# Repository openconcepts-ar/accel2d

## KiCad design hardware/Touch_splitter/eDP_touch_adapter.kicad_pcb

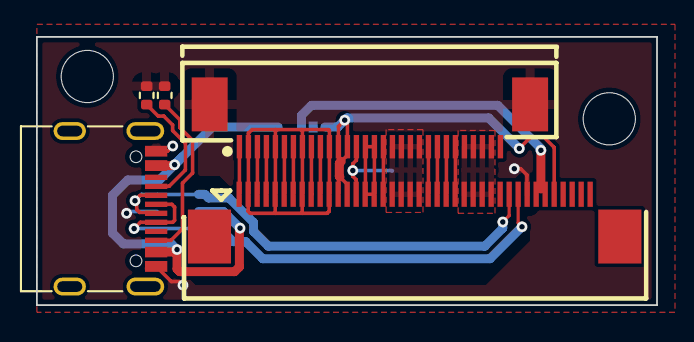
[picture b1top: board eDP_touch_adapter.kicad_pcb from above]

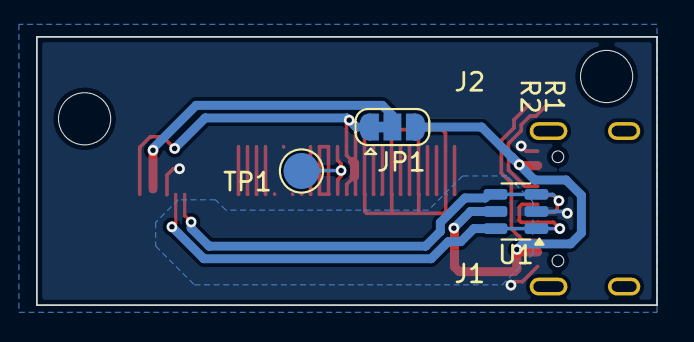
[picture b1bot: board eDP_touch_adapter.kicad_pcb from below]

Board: 2 copper layers, 34.4 x 14.9 mm, 10 parts (3 on the bottom side), 22 nets.

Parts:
H1, H2: MountingHole; MountingHole_2.2mm_M2_ISO7380
J1: Conn_01x40; FPC-SMD_40P-P0.50_L4.4-W25.6
J2: Conn_01x30; FPC-SMD_30P-P0.50_L4.4-W20.6
JP1: SolderJumper_3_Bridged12; SolderJumper-3_P1.3mm_Bridged12_RoundedPad1.0x1.5mm
R1, R2: 5.1k; R_0402_1005Metric
TP1: TestPoint_Small; TestPoint_Pad_D2.0mm
U1: USBLC6-2SC6; SOT-23-6
USB1: USB_C_Receptacle_USB2.0; USB_C_Receptacle_G-Switch_GT-USB-7010ASV

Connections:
+3V3: J1.12, J1.13, J1.36, J2.12, J2.13, JP1.1 (A)
+5V: JP1.3 (B), U1.5 (VBUS), USB1.A4 (VBUS), USB1.A9 (VBUS), USB1.B4 (VBUS), USB1.B9 (VBUS)
/AUX_N: J1.10, J2.10
/AUX_P: J1.9, J2.9
/BL_EN: J1.22, J2.22
/BL_GND: J1.18, J1.19, J1.20, J1.21, J2.18, J2.19, J2.20, J2.21
/BL_PWM: J1.23, J2.23
/BL_PWR: J1.26, J1.27, J1.28, J1.29, J2.26, J2.27, J2.28, J2.29
/EDP0_N: J1.6, J2.6
/EDP1_N: J1.3, J2.3
/EDP1_P: J1.4, J2.4
/EDPO_P: J1.7, J2.7
/HGND: J1.2, J1.5, J1.8, J1.11, J2.2, J2.5, J2.8, J2.11
/HPD: J1.17, J2.17
/LCD_GND: J1.15, J1.16, J2.15, J2.16
/TEST: J1.14, J2.14, TP1.1
/VTSP: J1.34, J1.35, JP1.2 (C)
GND: J1.33, J2.MP (MountPin), R1.2, R2.2, U1.2 (GND), USB1.A1 (GND), USB1.A12 (GND), USB1.B1 (GND), USB1.B12 (GND)
unnamed: R1.1, USB1.A5 (CC1)
unnamed: R2.1, USB1.B5 (CC2)
TP_D+: J1.32, U1.1 (I/O1), U1.6 (I/O1), USB1.A6 (D+), USB1.B6 (D+)
TP_D-: J1.31, U1.3 (I/O2), U1.4 (I/O2), USB1.A7 (D-), USB1.B7 (D-)

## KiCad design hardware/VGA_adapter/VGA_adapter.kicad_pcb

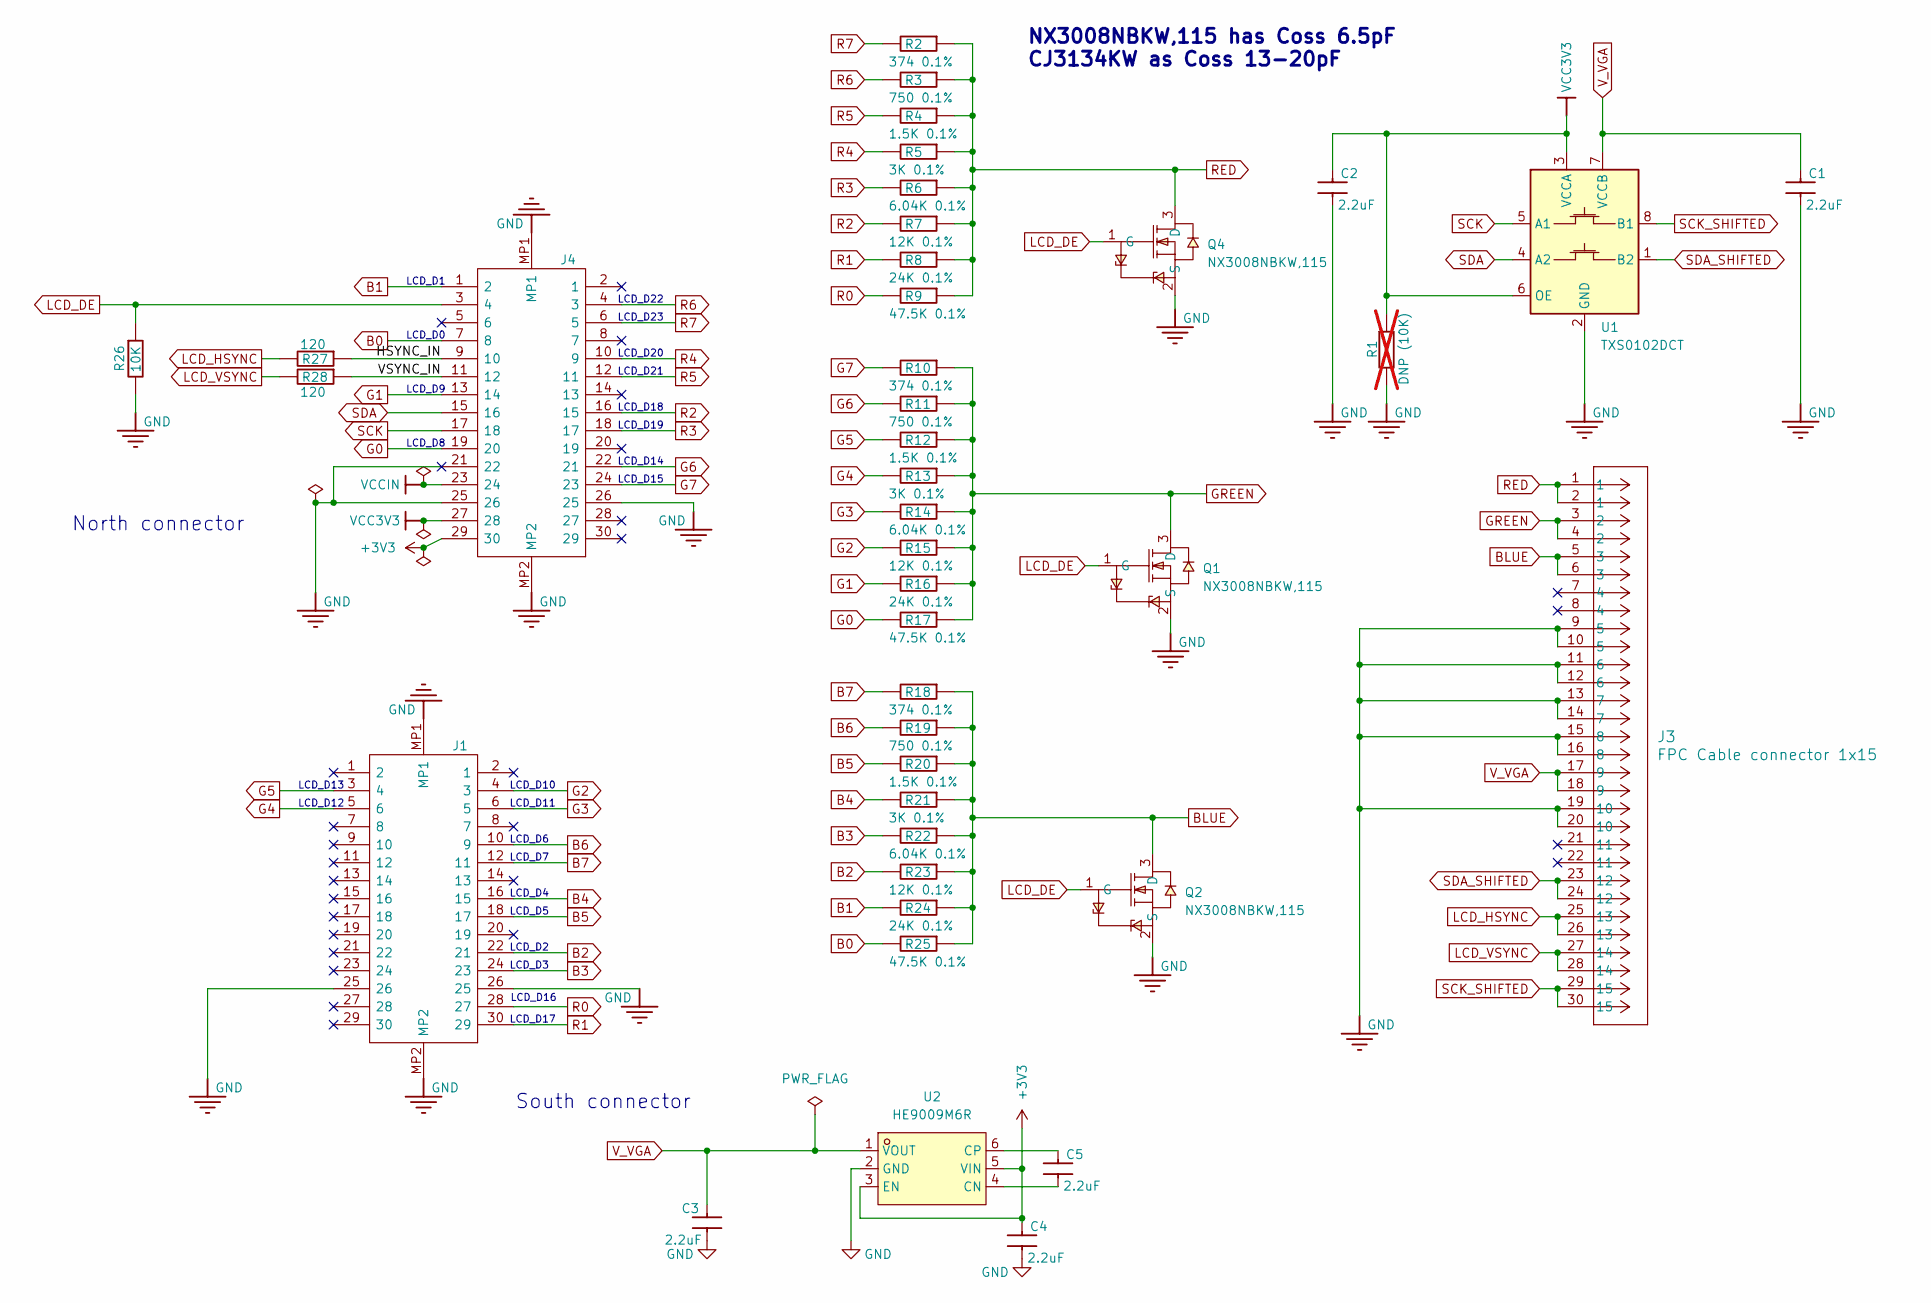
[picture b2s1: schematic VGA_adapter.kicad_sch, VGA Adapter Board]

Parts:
C1, C2, C3, C4, C5: 2.2uF; C_0402_1005Metric; LCSC Part Number C170151
J1, J4: DF12NB(3.0)-30DS-0.5V(51); CONN-SMD_30P-P0.50_HRS_DF12NB-3.0-30DP-0.5V; Manufacturer_Part_Number DF12NB(3.0)-30DP-0.5V(51); LCSC Part Number C2904115
J3: FPC Cable connector 1x15; TE Connectivity 1-1734248-5_ultralibrarian; LCSC Part Number C2922285
Q1, Q2, Q4: NX3008NBKW,115; SOT-323-3_L2.0-W1.3-P1.30-LS2.1-BR; MPN NX3008NBKW,115
R1: DNP (10K); R_0402_1005Metric; LCSC Part Number C25531; not fitted
R2, R10, R18: 374 0.1%; R_0402_1005Metric; LCSC Part Number C2681606
R3, R11, R19: 750 0.1%; R_0402_1005Metric; LCSC Part Number C852911
R4, R12, R20: 1.5K 0.1%; R_0402_1005Metric; LCSC Part Number C317917
R5, R13, R21: 3K 0.1%; R_0402_1005Metric; LCSC Part Number C281777
R6, R14, R22: 6.04K 0.1%; R_0402_1005Metric; LCSC Part Number C851092
R7, R15, R23: 12K 0.1%; R_0402_1005Metric; LCSC Part Number C319888
R8, R16, R24: 24K 0.1%; R_0402_1005Metric; LCSC Part Number C852665
R9, R17, R25: 47.5K 0.1%; R_0402_1005Metric; LCSC Part Number C2686413
R26: 10K; R_0402_1005Metric; LCSC Part Number C25531
R27, R28: 120; R_0402_1005Metric; LCSC Part Number C114758
U1: TXS0102DCT; SSOP-8_2.95x2.8mm_P0.65mm
U2: HE9009M6R; SOT-23-6; MPN HE9009M6R

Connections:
+3V3: C4.1, J4.29 (30), U2.3 (EN), U2.5 (VIN)
/HSYNC_IN: J4.9 (10), R27.1
/VSYNC_IN: J4.11 (12), R28.1
B0: J4.7 (8), R25.2
B1: J4.1 (2), R24.2
B2: J1.22 (21), R23.2
B3: J1.24 (23), R22.2
B4: J1.16 (15), R21.2
B5: J1.18 (17), R20.2
B6: J1.10 (9), R19.2
B7: J1.12 (11), R18.2
BLUE: J3.5 (3), J3.6 (3), Q2.3 (D), R18.1, R19.1, R20.1, R21.1, R22.1, R23.1, R24.1, R25.1
G0: J4.19 (20), R17.2
G1: J4.13 (14), R16.2
G2: J1.4 (3), R15.2
G3: J1.6 (5), R14.2
G4: J1.5 (6), R13.2
G5: J1.3 (4), R12.2
G6: J4.22 (21), R11.2
G7: J4.24 (23), R10.2
GND: C1.2, C2.2, C3.2, C4.2, J1.25 (26), J1.26 (25), J1.MP1, J1.MP2, J3.9 (5), J3.10 (5), J3.11 (6), J3.12 (6), J3.13 (7), J3.14 (7), J3.15 (8), J3.16 (8), J3.19 (10), J3.20 (10), J4.21 (22), J4.25 (26), J4.26 (25), J4.MP1, J4.MP2, Q1.2 (S), Q2.2 (S), Q4.2 (S), R1.2, R26.2, U1.2 (GND), U2.2 (GND)
GREEN: J3.3 (2), J3.4 (2), Q1.3 (D), R10.1, R11.1, R12.1, R13.1, R14.1, R15.1, R16.1, R17.1
LCD_DE: J4.3 (4), Q1.1 (G), Q2.1 (G), Q4.1 (G), R26.1
LCD_HSYNC: J3.25 (13), J3.26 (13), R27.2
LCD_VSYNC: J3.27 (14), J3.28 (14), R28.2
unnamed: C5.2, U2.4 (CN)
unnamed: C5.1, U2.6 (CP)
R0: J1.28 (27), R9.2
R1: J1.30 (29), R8.2
R2: J4.16 (15), R7.2
R3: J4.18 (17), R6.2
R4: J4.10 (9), R5.2
R5: J4.12 (11), R4.2
R6: J4.4 (3), R3.2
R7: J4.6 (5), R2.2
RED: J3.1, J3.2 (1), Q4.3 (D), R2.1, R3.1, R4.1, R5.1, R6.1, R7.1, R8.1, R9.1
SCK: J4.17 (18), U1.5 (A1)
SCK_SHIFTED: J3.29 (15), J3.30 (15), U1.8 (B1)
SDA: J4.15 (16), U1.4 (A2)
SDA_SHIFTED: J3.23 (12), J3.24 (12), U1.1 (B2)
VCC3V3: C2.1, J4.27 (28), R1.1, U1.3 (VCCA), U1.6 (OE)
VCCIN: J4.23 (24)
V_VGA: C1.1, C3.1, J3.17 (9), J3.18 (9), U1.7 (VCCB), U2.1 (VOUT)

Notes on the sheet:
LCD_D12
South connector
LCD_D15
LCD_D5
North connector
LCD_D1
LCD_D9
LCD_D2
LCD_D18
LCD_D7
LCD_D3
LCD_D16
LCD_D0
LCD_D19
LCD_D22
LCD_D23
LCD_D20
LCD_D21
LCD_D13
LCD_D11
LCD_D17
LCD_D6
LCD_D4
LCD_D14
LCD_D8
LCD_D10
NX3008NBKW,115 has Coss 6.5pF CJ3134KW as Coss 13-20pF

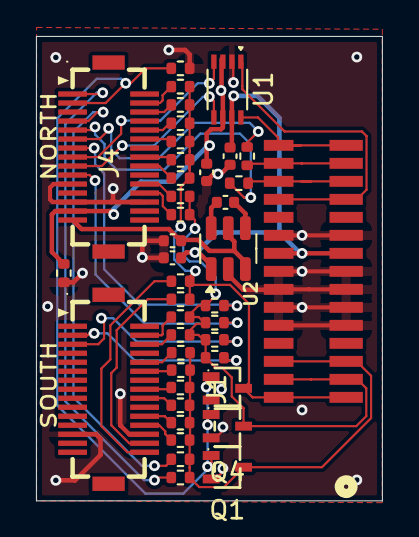
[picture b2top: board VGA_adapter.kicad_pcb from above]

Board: 2 copper layers, 19.2 x 25.8 mm, 41 parts (0 on the bottom side), 42 nets.

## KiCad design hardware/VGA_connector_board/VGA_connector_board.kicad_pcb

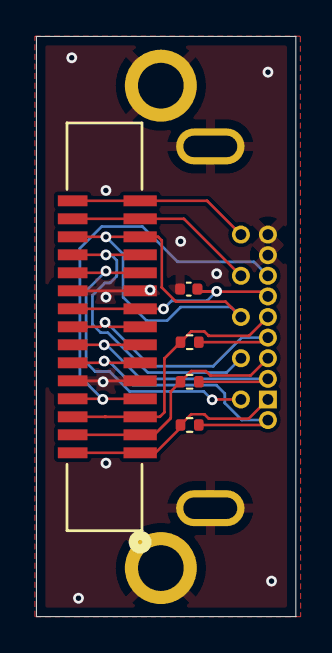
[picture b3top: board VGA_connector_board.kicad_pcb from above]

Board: 2 copper layers, 14.4 x 32.2 mm, 8 parts (0 on the bottom side), 14 nets.

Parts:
C1: 0.1uF; C_0402_1005Metric
J1: FPC Cable connector 1x15; TE Connectivity 1-1734248-5_ultralibrarian
MH1, MH2: (no value)
R1, R2, R3: 150 1%; R_0402_1005Metric
VGA1: DE15 female; XKB_Connectivity_DOR02-15-X

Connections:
/5V0: C1.1, J1.17 (9), J1.18 (9), VGA1.9
/BLUE: J1.5 (3), J1.6 (3), R1.2, VGA1.3
/BLUE_RTN: J1.15 (8), J1.16 (8), R1.1, VGA1.8
/GREEN: J1.3 (2), J1.4 (2), R2.2, VGA1.2
/GREEN_RTN: J1.13 (7), J1.14 (7), R2.1, VGA1.7
/HSYNC: J1.25 (13), J1.26 (13), VGA1.13
/NC_PIN4: J1.7 (4), J1.8 (4), VGA1.4
/NC_PIN11: J1.21 (11), J1.22 (11), VGA1.11
/RED: J1.1, J1.2 (1), R3.2, VGA1.1
/RED_RTN: J1.11 (6), J1.12 (6), R3.1, VGA1.6
/SCK: J1.29 (15), J1.30 (15), VGA1.15
/SDA: J1.23 (12), J1.24 (12), VGA1.12
/VSYNC: J1.27 (14), J1.28 (14), VGA1.14
GND: C1.2, J1.9 (5), J1.10 (5), J1.19 (10), J1.20 (10), MH1.18, MH2.18, VGA1.5, VGA1.10, VGA1.16, VGA1.17

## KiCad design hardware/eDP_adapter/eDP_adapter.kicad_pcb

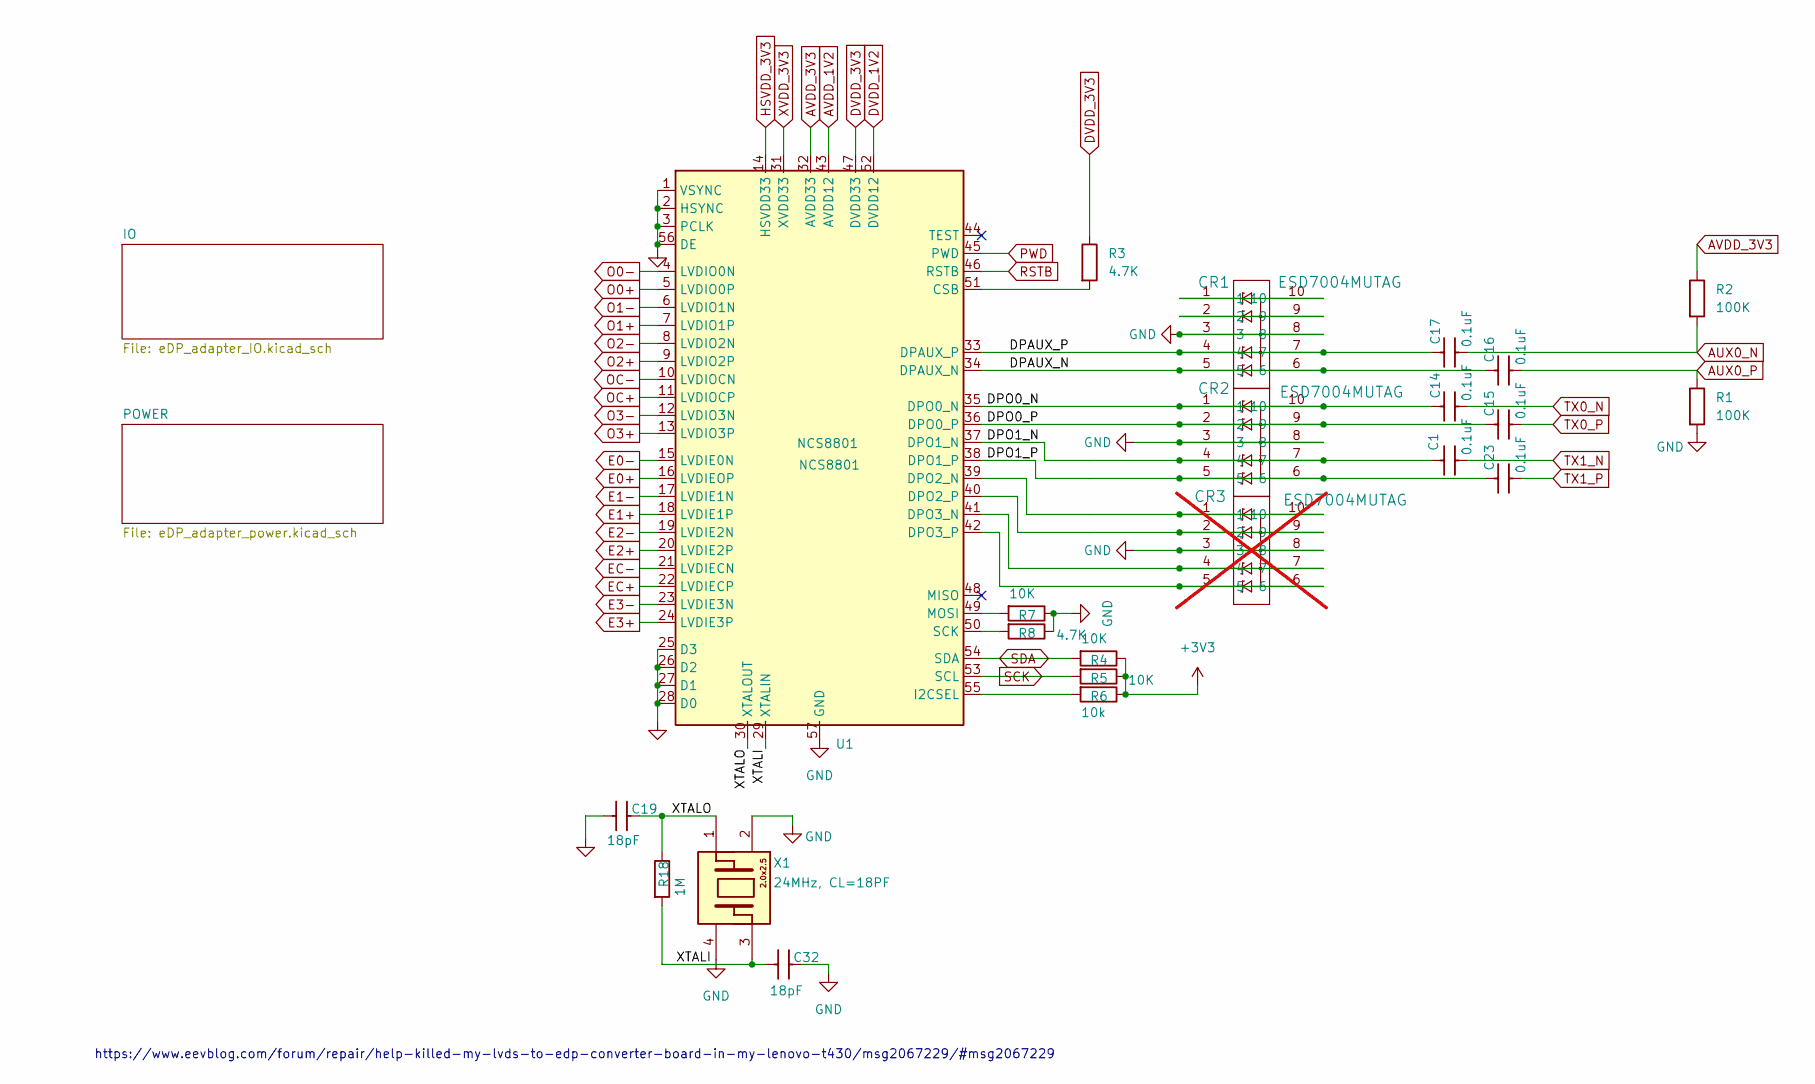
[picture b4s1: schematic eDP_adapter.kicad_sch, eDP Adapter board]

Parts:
C1, C14, C17, C23: 0.1uF; C_0402_1005Metric
C15, C16: 0.1uF; C_0402_1005Metric; LCSC Part Number C60474
C19, C32: 18pF; C_0402_1005Metric
CR1, CR2: ESD7004MUTAG; UDFN10_517BB_ONS-L; LCSC Part Number C2931115
CR3: ESD7004MUTAG; UDFN10_517BB_ONS-L; LCSC Part Number C2931115; not fitted
R1, R2: 100K; R_0402_1005Metric
R3, R8: 4.7K; R_0402_1005Metric
R4, R5, R7: 10K; R_0402_1005Metric
R6: 10k; R_0402_1005Metric
R18: 1M; R_0402_1005Metric
U1: NCS8801; QFN-56-1EP_7x7mm_P0.4mm_EP4x4mm; MPN NCS8801; LCSC Part Number C9900208623
X1: 24MHz, CL=18PF; Crystal_SMD_2520-4Pin_2.5x2.0mm; LCSC Part Number C371128

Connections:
+3V3: R4.1, R5.1, R6.1; also elsewhere on the board
/DPAUX_N: C16.1, CR1.5, CR1.6, U1.34 (DPAUX_N)
/DPAUX_P: C17.1, CR1.4, CR1.7, U1.33 (DPAUX_P)
/DPO0_N: C14.1, CR2.1, CR2.10, U1.35 (DPO0_N)
/DPO0_P: C15.1, CR2.2, CR2.9, U1.36 (DPO0_P)
/DPO1_N: C1.1, CR2.4, CR2.7, U1.37 (DPO1_N)
/DPO1_P: C23.1, CR2.5, CR2.6, U1.38 (DPO1_P)
/XTALI: C32.2, R18.2, U1.29 (XTALIN), X1.3 (X2)
/XTALO: C19.1, R18.1, U1.30 (XTALOUT), X1.1 (X1)
AUX0_N: C17.2, R2.2; also elsewhere on the board
AUX0_P: C16.2, R1.1; also elsewhere on the board
AVDD_1V2: U1.43 (AVDD12); also elsewhere on the board
AVDD_3V3: R2.1, U1.32 (AVDD33); also elsewhere on the board
DVDD_1V2: U1.52 (DVDD12); also elsewhere on the board
DVDD_3V3: R3.1, U1.47 (DVDD33); also elsewhere on the board
E0+: U1.16 (LVDIEOP); also elsewhere on the board
E0-: U1.15 (LVDIE0N); also elsewhere on the board
E1+: U1.18 (LVDIE1P); also elsewhere on the board
E1-: U1.17 (LVDIE1N); also elsewhere on the board
E2+: U1.20 (LVDIE2P); also elsewhere on the board
E2-: U1.19 (LVDIE2N); also elsewhere on the board
E3+: U1.24 (LVDIE3P); also elsewhere on the board
E3-: U1.23 (LVDIE3N); also elsewhere on the board
EC+: U1.22 (LVDIECP); also elsewhere on the board
EC-: U1.21 (LVDIECN); also elsewhere on the board
HSVDD_3V3: U1.14 (HSVDD33); also elsewhere on the board
unnamed: CR1.1, CR1.10
unnamed: CR1.2, CR1.9
unnamed: R3.2, U1.51 (CSB)
unnamed: CR3.1, CR3.10, U1.39 (DPO2_N)
unnamed: CR3.2, CR3.9, U1.40 (DPO2_P)
unnamed: CR3.4, CR3.7, U1.41 (DPO3_N)
unnamed: CR3.5, CR3.6, U1.42 (DPO3_P)
unnamed: R6.2, U1.55 (I2CSEL)
unnamed: R7.2, U1.49 (MOSI)
unnamed: R8.2, U1.50 (SCK)
O0+: U1.5 (LVDIO0P); also elsewhere on the board
O0-: U1.4 (LVDIO0N); also elsewhere on the board
O1+: U1.7 (LVDIO1P); also elsewhere on the board
O1-: U1.6 (LVDIO1N); also elsewhere on the board
O2+: U1.9 (LVDIO2P); also elsewhere on the board
O2-: U1.8 (LVDIO2N); also elsewhere on the board
O3+: U1.13 (LVDIO3P); also elsewhere on the board
O3-: U1.12 (LVDIO3N); also elsewhere on the board
OC+: U1.11 (LVDIOCP); also elsewhere on the board
OC-: U1.10 (LVDIOCN); also elsewhere on the board
PWD: U1.45 (PWD); also elsewhere on the board
RSTB: U1.46 (RSTB); also elsewhere on the board
SCK: R5.2, U1.53 (SCL); also elsewhere on the board
SDA: R4.2, U1.54 (SDA); also elsewhere on the board
TX0_N: C14.2; also elsewhere on the board
TX0_P: C15.2; also elsewhere on the board
TX1_N: C1.2; also elsewhere on the board
TX1_P: C23.2; also elsewhere on the board
XVDD_3V3: U1.31 (XVDD33); also elsewhere on the board

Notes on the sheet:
https://www.eevblog.com/forum/repair/help-killed-my-lvds-to-edp-converter-board-in-my-lenovo-t430/msg2067229/#msg2067229

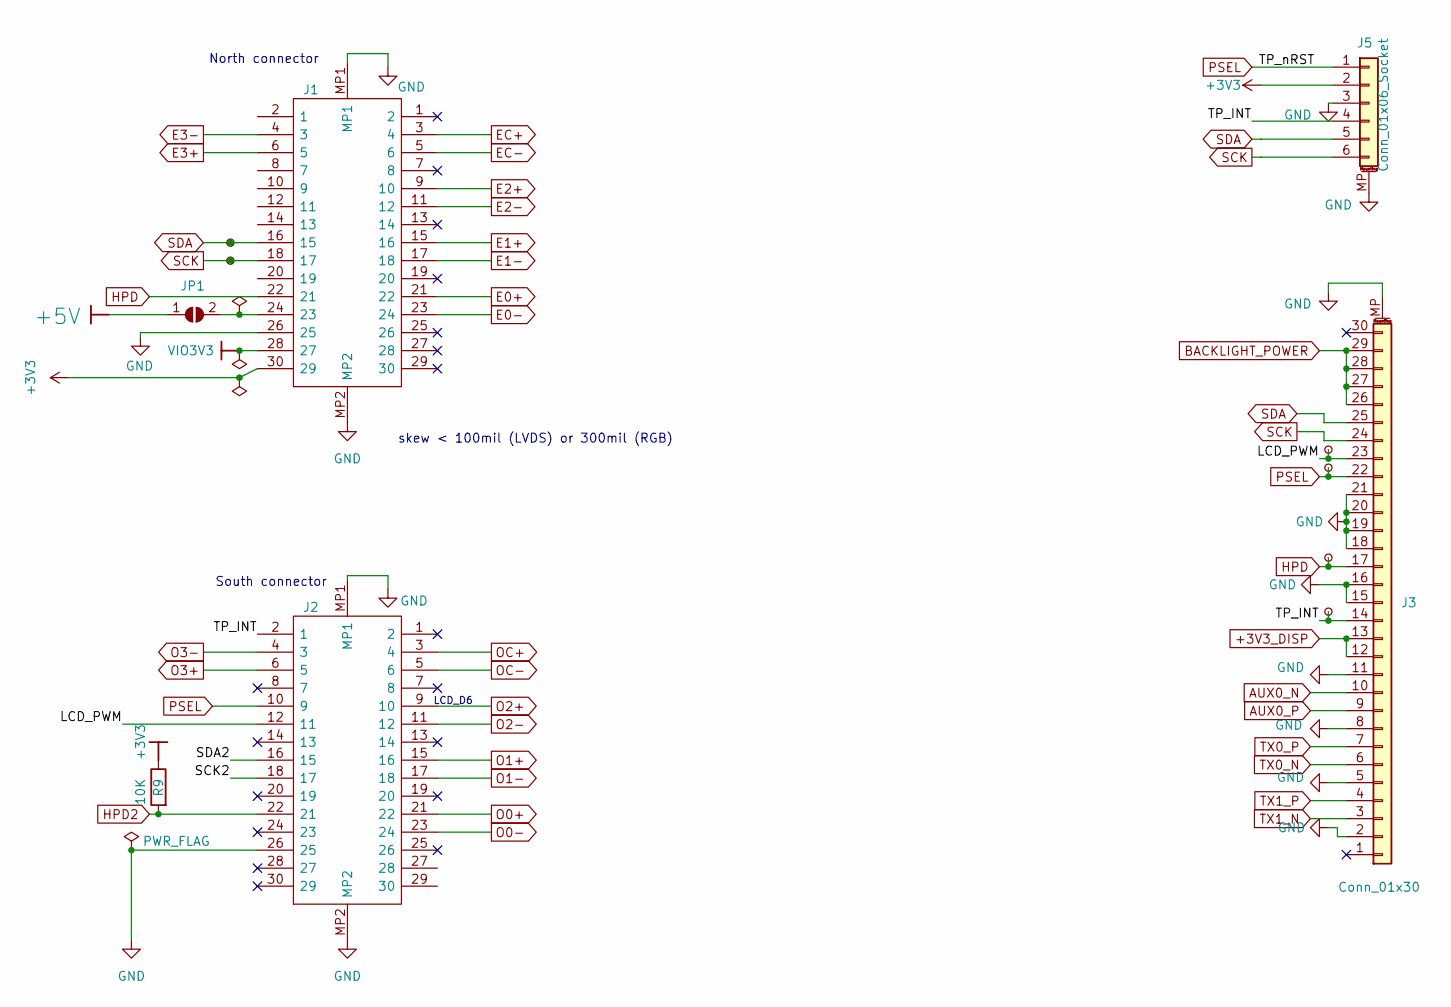
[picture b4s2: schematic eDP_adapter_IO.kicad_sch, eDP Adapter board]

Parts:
J1, J2: DF12NB(3.0)-30DS-0.5V(51); DF12NB3030DP05V51; Manufacturer_Part_Number DF12NB(3.0)-30DP-0.5V(51); LCSC Part Number C2904115
J3: Conn_01x30; FPC-SMD_30P-P0.50_FPC-0.5FX-30PWBH15; MPN FPC-0.5FX-30PWBH15
J5: Conn_01x06_Socket; CONN-SMD_527450697; MPN 527450697
JP1: SolderJumper_2_Open; SolderJumper-2_P1.3mm_Open_RoundedPad1.0x1.5mm
R9: 10K; R_0402_1005Metric
TP1, TP2, TP4, TP5, TP6, TP7: TestPoint_Small; TestPoint_Pad_D1.0mm

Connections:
+3V3: J1.30 (29), J5.2, R9.1; also elsewhere on the board
+3V3_DISP: J3.12, J3.13; also elsewhere on the board
+5V: JP1.1 (A); also elsewhere on the board
/IO/LCD_PWM: J2.12 (11), J3.23, TP4.1
/IO/SCK2: J2.18 (17)
/IO/SDA2: J2.16 (15)
/IO/TP_INT: J2.2 (1), J3.14, J5.4, TP7.1
AUX0_N: J3.10; also elsewhere on the board
AUX0_P: J3.9; also elsewhere on the board
BACKLIGHT_POWER: J3.26, J3.27, J3.28, J3.29; also elsewhere on the board
E0+: J1.21 (22); also elsewhere on the board
E0-: J1.23 (24); also elsewhere on the board
E1+: J1.15 (16); also elsewhere on the board
E1-: J1.17 (18); also elsewhere on the board
E2+: J1.9 (10); also elsewhere on the board
E2-: J1.11 (12); also elsewhere on the board
E3+: J1.6 (5); also elsewhere on the board
E3-: J1.4 (3); also elsewhere on the board
EC+: J1.3 (4); also elsewhere on the board
EC-: J1.5 (6); also elsewhere on the board
HPD: J1.22 (21), J3.17, TP6.1
HPD2: J2.22 (21), R9.2
unnamed: J1.24 (23), JP1.2 (B)
O0+: J2.21 (22); also elsewhere on the board
O0-: J2.23 (24); also elsewhere on the board
O1+: J2.15 (16); also elsewhere on the board
O1-: J2.17 (18); also elsewhere on the board
O2+: J2.9 (10); also elsewhere on the board
O2-: J2.11 (12); also elsewhere on the board
O3+: J2.6 (5); also elsewhere on the board
O3-: J2.4 (3); also elsewhere on the board
OC+: J2.3 (4); also elsewhere on the board
OC-: J2.5 (6); also elsewhere on the board
PSEL: J2.10 (9), J3.22, J5.1, TP5.1
SCK: J1.18 (17), J3.24, J5.6, TP2.1; also elsewhere on the board
SDA: J1.16 (15), J3.25, J5.5, TP1.1; also elsewhere on the board
TX0_N: J3.6; also elsewhere on the board
TX0_P: J3.7; also elsewhere on the board
TX1_N: J3.3; also elsewhere on the board
TX1_P: J3.4; also elsewhere on the board
VIO3V3: J1.28 (27); also elsewhere on the board

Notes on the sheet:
South connector
skew < 100mil (LVDS) or 300mil (RGB)
North connector
LCD_D6

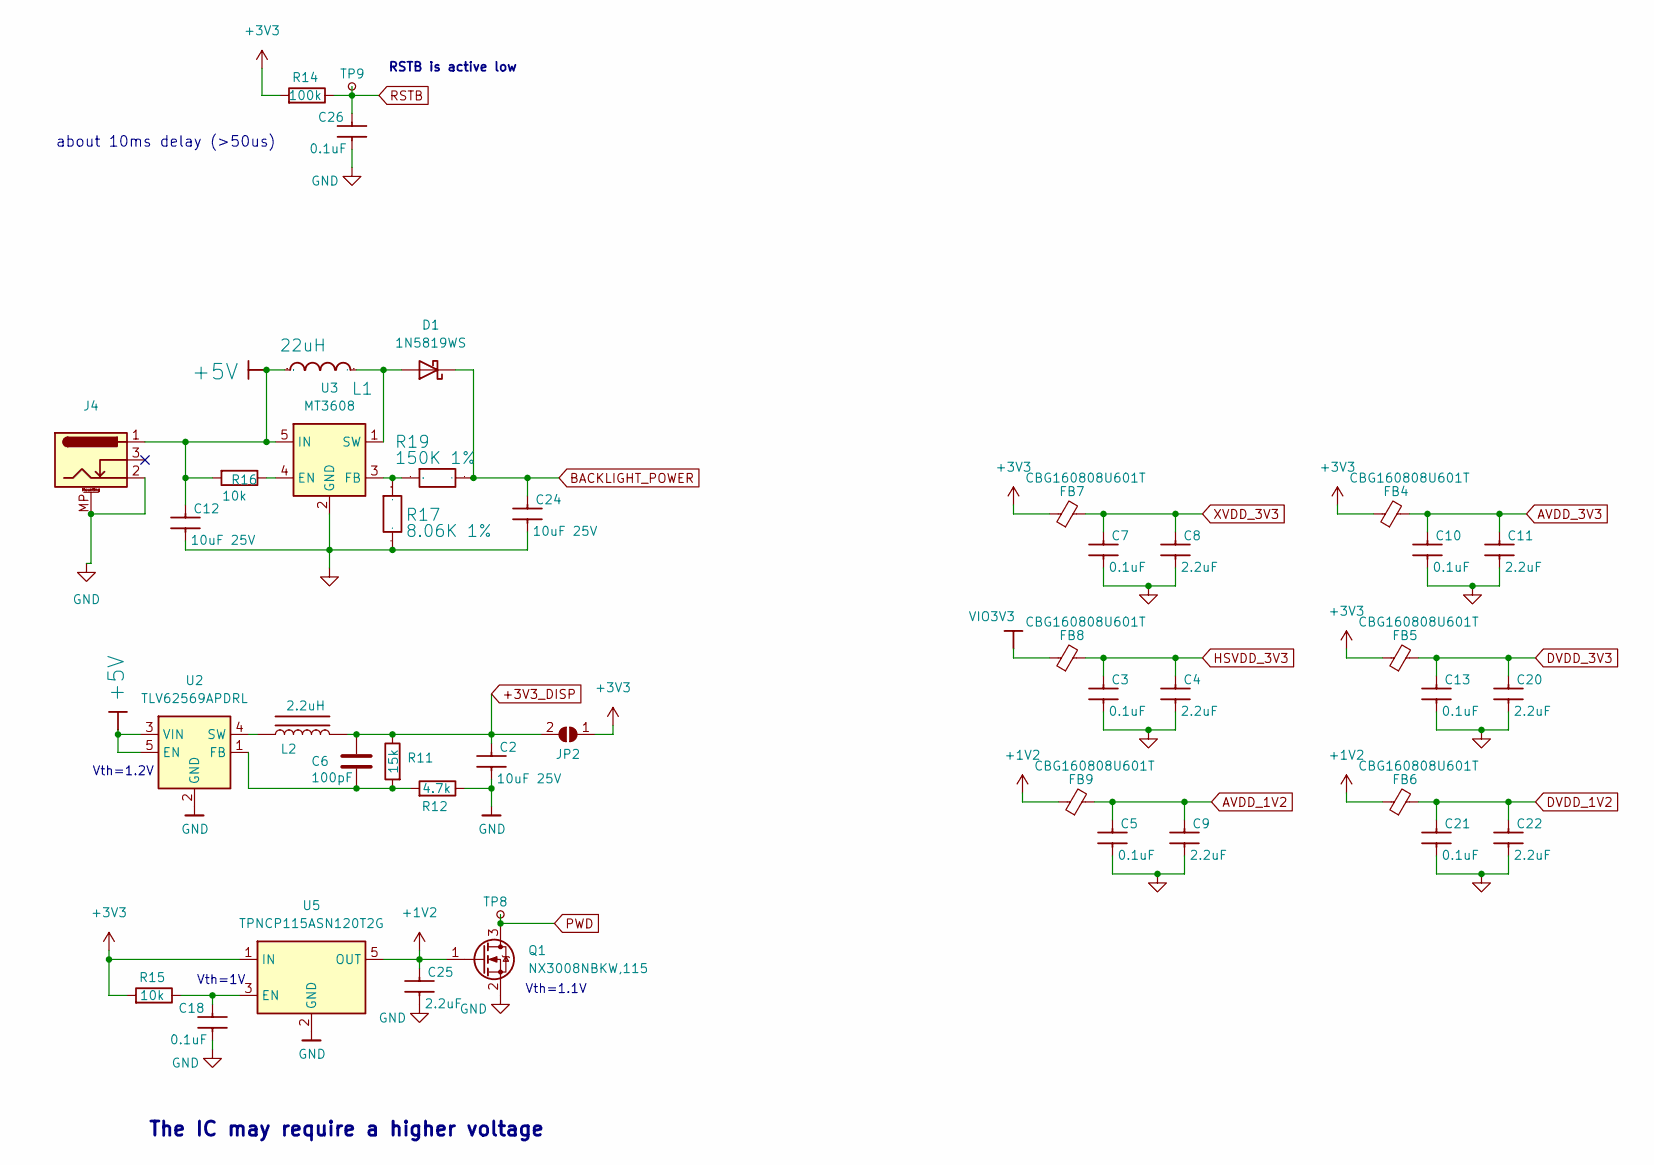
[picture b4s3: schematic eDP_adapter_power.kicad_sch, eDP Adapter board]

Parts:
C2, C12, C24: 10uF 25V; C_0805_2012Metric; MPN TCC0805X5R106K250FT
C3: 0.1uF; C_0402_1005Metric; LCSC Part Number C60474
C4, C8, C9, C11, C20, C22, C25: 2.2uF; C_0402_1005Metric; LCSC Part Number C170151
C5, C7, C10, C13, C18, C21, C26: 0.1uF; C_0402_1005Metric
C6: 100pF; C_0201_0603Metric; MPN GRM033R61C103KA12D
D1: 1N5819WS; D_SOD-323; MPN 1N5819WS
FB4, FB5, FB6, FB7, FB8, FB9: CBG160808U601T; L_0603_1608Metric; LCSC Part Number C73326
J4: Barrel_Jack_MountingPin; DC-IN-SMD_DC-045A-13A; MPN DC-045A-13A
JP2: SolderJumper_2_Open; SolderJumper-2_P1.3mm_Open_RoundedPad1.0x1.5mm
L1: 22uH; L_Cenker_CKCS4020; LCSC Part Number C5125979
L2: 2.2uH; Murata_DFE201612P-2R2M=P2; LCSC Part Number C79317
Q1: NX3008NBKW,115; SOT-323_SC-70; MPN NX3008NBKW,115
R11: 15k; R_0201_0603Metric; MPN RC0201FR-07100KL
R12: 4.7k; R_0201_0603Metric; MPN RC0201FR-07100KL
R14: 100k; R_0402_1005Metric
R15, R16: 10k; R_0402_1005Metric
R17: 8.06K 1%; R_0402_1005Metric; MPN RC0402FR-078K06L
R19: 150K 1%; R_0402_1005Metric
TP8, TP9: TestPoint_Small; TestPoint_Pad_D1.0mm
U2: TLV62569APDRL; SOT-563; MPN TLV62569APDRLR
U3: MT3608; SOT-23-6; MPN MT3608
U5: TPNCP115ASN120T2G; SOT-23-5; MPN TPNCP115ASN120T2G

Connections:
+3V3: FB4.1, FB5.1, FB7.1, JP2.1 (A), R14.2, R15.2, U5.1 (IN); also elsewhere on the board
+3V3_DISP: C2.1, C6.2, JP2.2 (B), L2.1, R11.1; also elsewhere on the board
+5V: C12.1, J4.1, L1.1, R16.2, U2.3 (VIN), U2.5 (EN), U3.5 (IN); also elsewhere on the board
AVDD_1V2: C5.1, C9.1, FB9.2; also elsewhere on the board
AVDD_3V3: C10.1, C11.1, FB4.2; also elsewhere on the board
BACKLIGHT_POWER: C24.1, D1.1 (K), R19.2; also elsewhere on the board
DVDD_1V2: C21.1, C22.1, FB6.2; also elsewhere on the board
DVDD_3V3: C13.1, C20.1, FB5.2; also elsewhere on the board
HSVDD_3V3: C3.1, C4.1, FB8.2; also elsewhere on the board
unnamed: D1.2 (A), L1.2, U3.1 (SW)
unnamed: C6.1, R11.2, R12.2, U2.1 (FB)
unnamed: L2.2, U2.4 (SW)
unnamed: R16.1, U3.4 (EN)
unnamed: R17.1, R19.1, U3.3 (FB)
unnamed: C18.1, R15.1, U5.3 (EN)
PWD: Q1.3 (D), TP8.1; also elsewhere on the board
RSTB: C26.1, R14.1, TP9.1; also elsewhere on the board
VIO3V3: FB8.1; also elsewhere on the board
XVDD_3V3: C7.1, C8.1, FB7.2; also elsewhere on the board

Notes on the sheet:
Vth=1.1V
Vth=1V
Vth=1.2V
RSTB is active low
about 10ms delay (>50us)
The IC may require a higher voltage

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
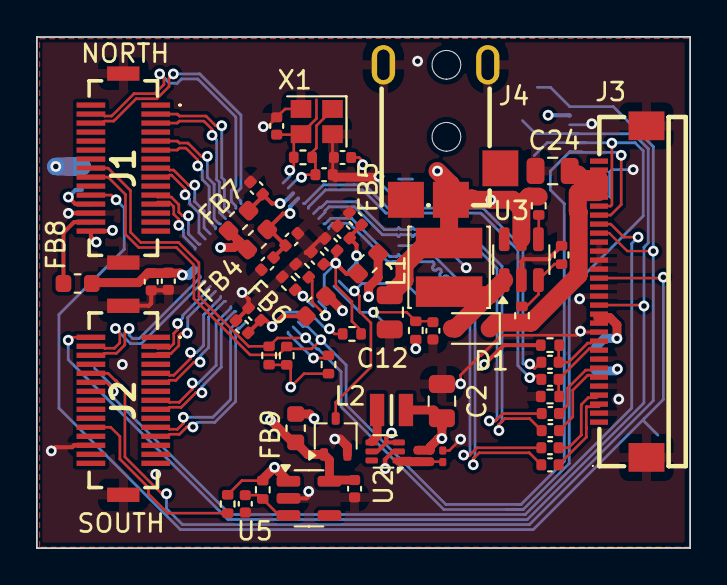
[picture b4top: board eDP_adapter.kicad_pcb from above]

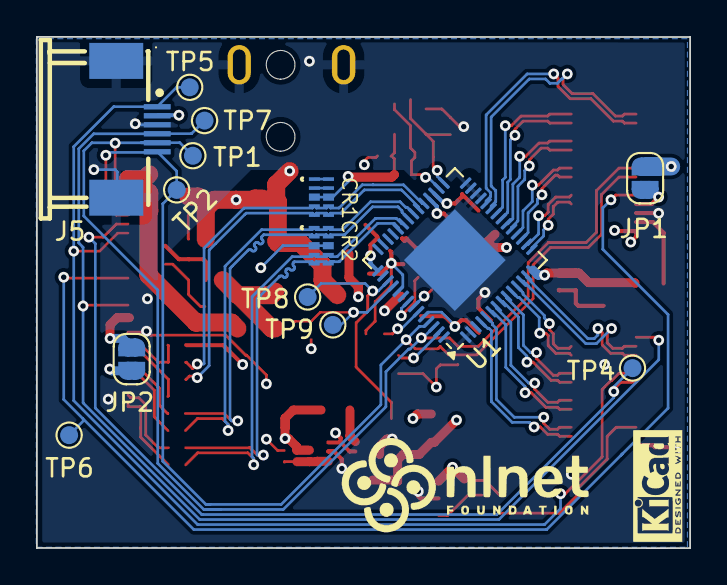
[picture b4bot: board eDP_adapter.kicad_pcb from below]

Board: 4 copper layers, 36.3 x 28.4 mm, 76 parts (14 on the bottom side), 69 nets.

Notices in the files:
hardware/VGA_adapter/VGA_adapter.kicad_pcb:
Copyright (C) Victor Suarez Rovere
License:  CERN OHL-S
hardware/VGA_adapter/VGA_adapter.kicad_sch:
Copyright (C) 2023-2024 Victor Suarez Rovere
hardware/VGA_connector_board/VGA_connector_board.kicad_pcb:
CERN OHL-S
hardware/eDP_adapter/eDP_adapter.kicad_sch:
Copyright (C) 2025-2026 Victor Suarez Rovere
